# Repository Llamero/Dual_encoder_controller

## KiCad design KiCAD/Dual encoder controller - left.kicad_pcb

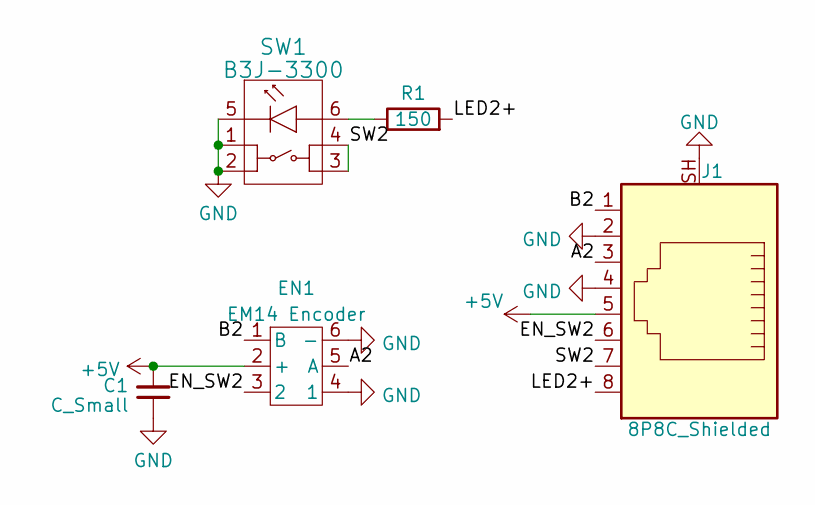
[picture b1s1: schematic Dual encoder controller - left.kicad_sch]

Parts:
C1: C_Small; C_Rect_L4.0mm_W2.5mm_P2.50mm; Part RCER71H105K2DBH03A
EN1: EM14 Encoder; EM14R0B-M25-L064S; Part EM14R0B-M25-L064S
J1: 8P8C_Shielded; ASSMANN_A-2004-2-4-LPS-N-R; Part A-2004-2-4-LPS-N-R
R1: 150; R_Axial_DIN0207_L6.3mm_D2.5mm_P7.62mm_Horizontal; Part LR1F150R
SW1: B3J-3300; Part B3J-3300

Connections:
+5V: C1.2, EN1.2 (+), J1.5
/A2: EN1.5 (A), J1.3
/B2: EN1.1 (B), J1.1
/EN_SW2: EN1.3 (2), J1.6
/LED2+: J1.8, R1.2
/SW2: J1.7, SW1.3, SW1.4
GND: C1.1, EN1.4 (1), EN1.6 (-), J1.2, J1.4, J1.SH, SW1.1, SW1.2, SW1.5
unnamed: R1.1, SW1.6

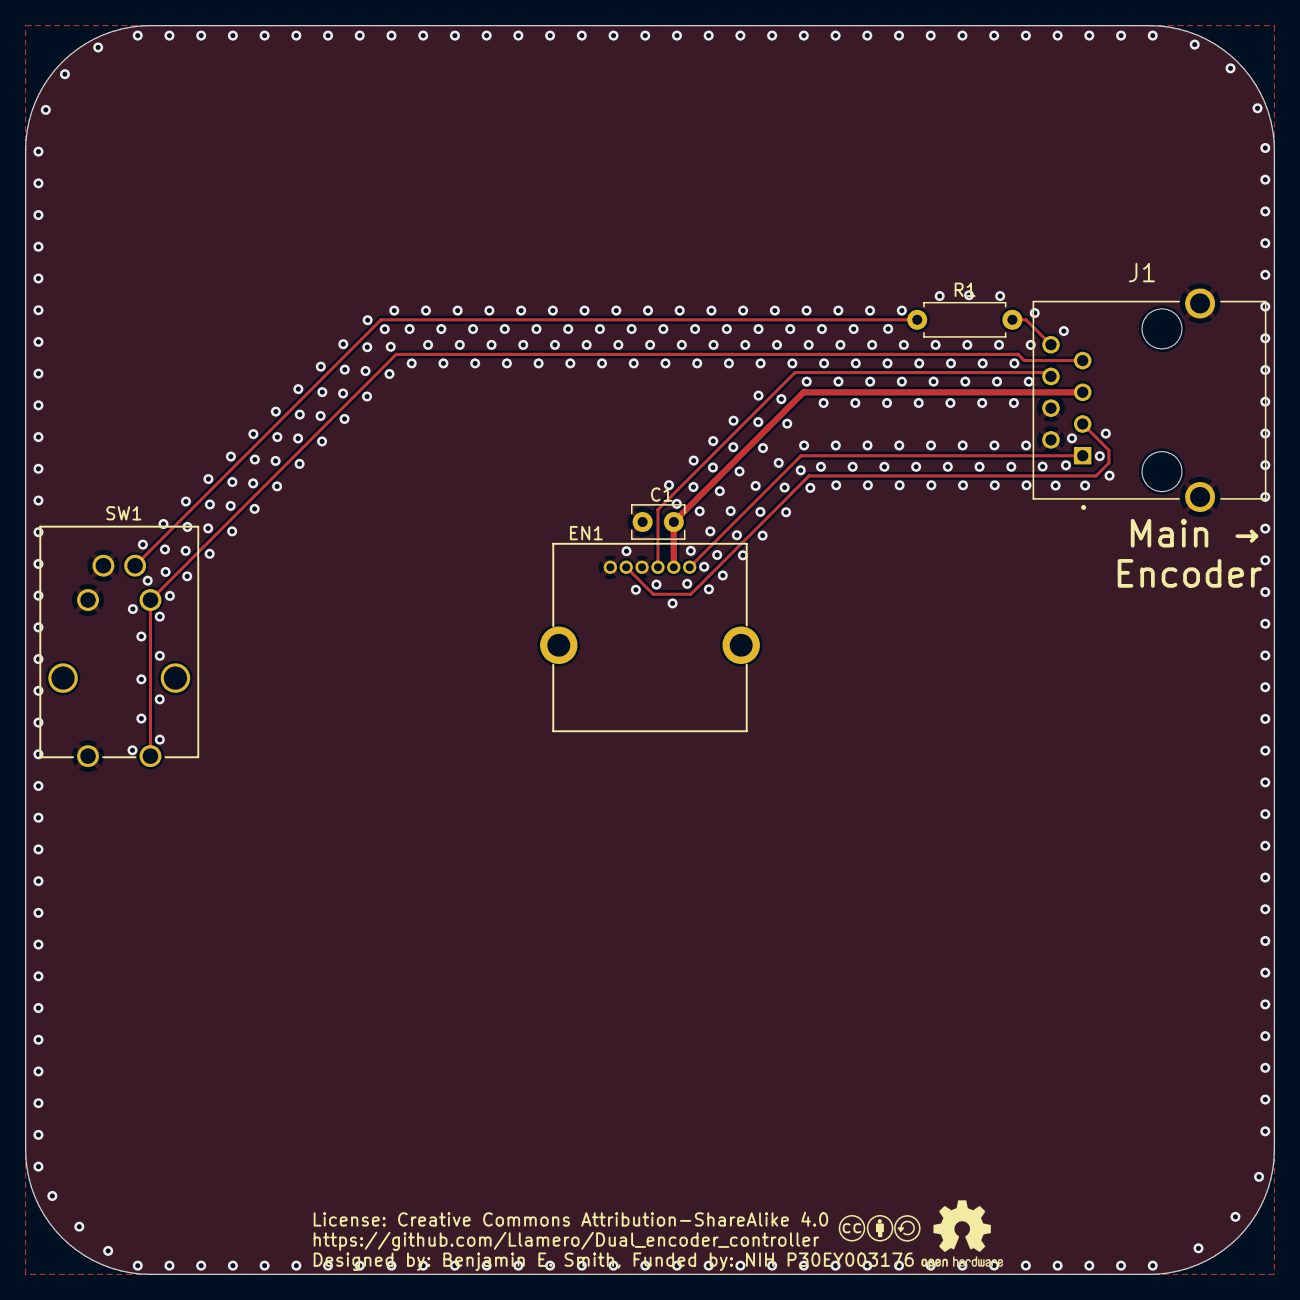
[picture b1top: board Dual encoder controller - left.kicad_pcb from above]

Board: 2 copper layers, 100.0 x 100.0 mm, 7 parts (0 on the bottom side), 8 nets.

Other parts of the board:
LOGO1: CC license; Creative_commons_license
LOGO3: OSHW Logo; OSHW-Logo2_7.3x6mm_SilkScreen

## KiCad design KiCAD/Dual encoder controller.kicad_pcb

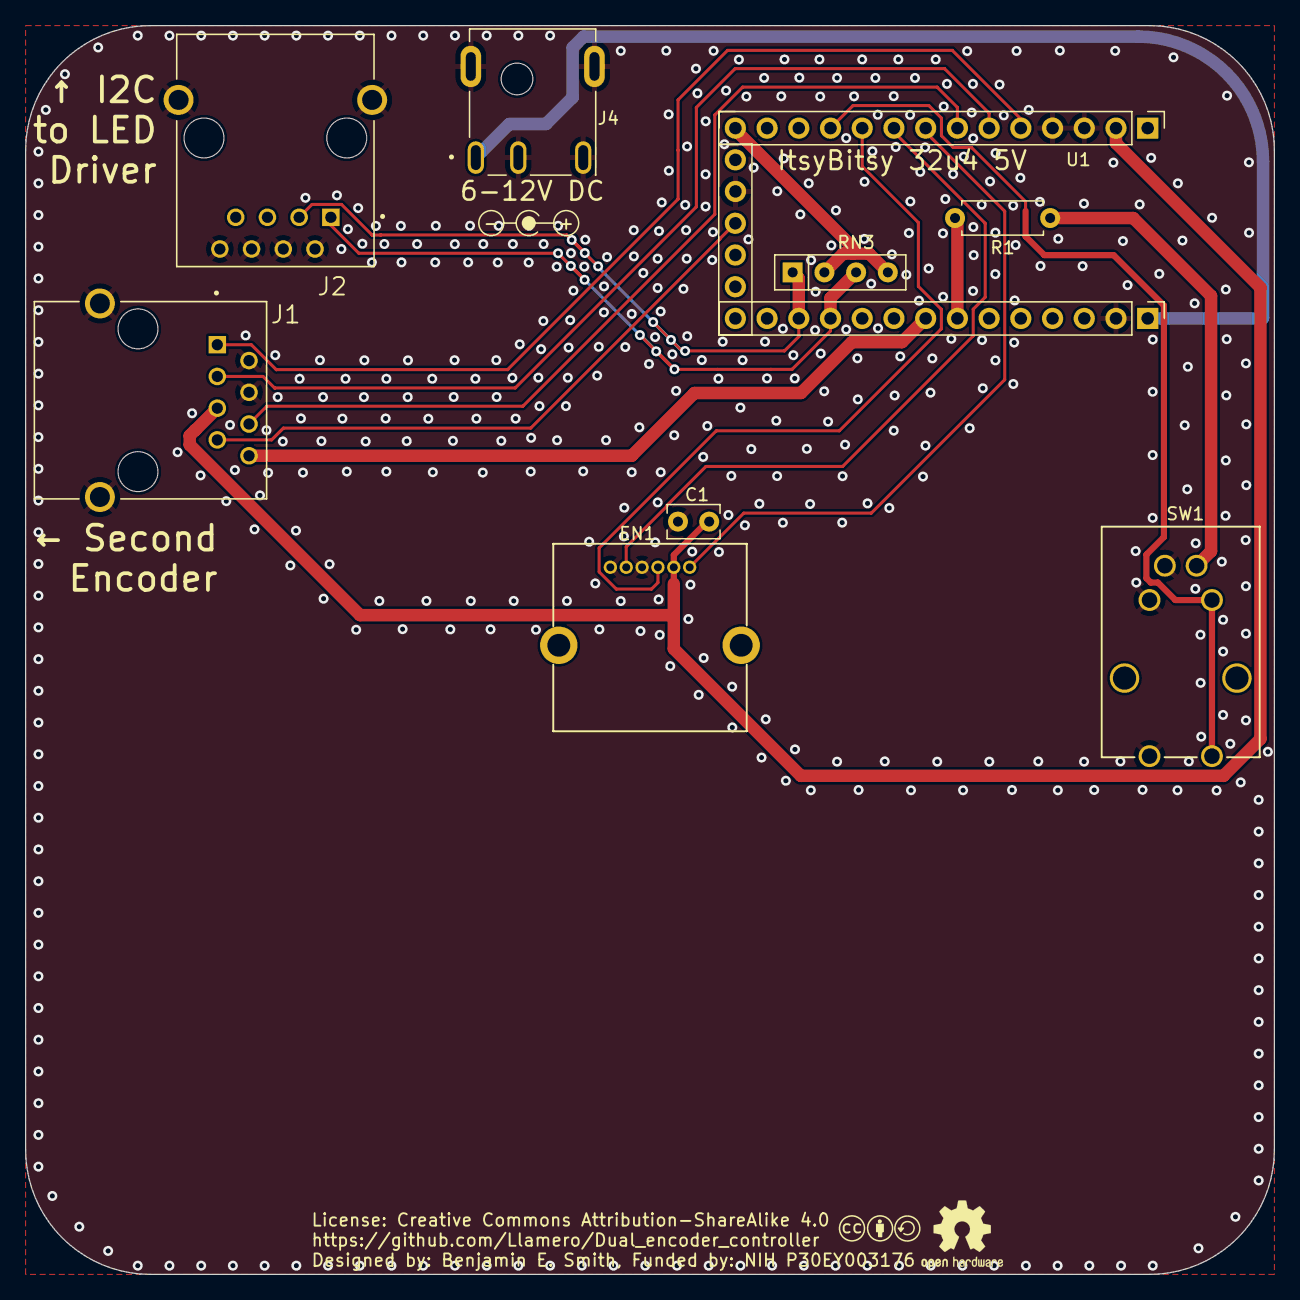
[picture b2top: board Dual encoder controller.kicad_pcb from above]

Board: 2 copper layers, 100.0 x 100.0 mm, 12 parts (0 on the bottom side), 17 nets.

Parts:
C1: C_Small; C_Rect_L4.0mm_W2.5mm_P2.50mm
EN1: EM14 Encoder; EM14R0B-M25-L064S
J1, J2: 8P8C_Shielded; ASSMANN_A-2004-2-4-LPS-N-R
J4: 2.5x5.5 Barrel Jack; TENSILITY_54-00128-DC Jack
LOGO1: CC license; Creative_commons_license
LOGO2: Jack Polarity; Polarity_Center_Positive
LOGO3: OSHW Logo; OSHW-Logo2_7.3x6mm_SilkScreen
R1: 150; R_Axial_DIN0207_L6.3mm_D2.5mm_P7.62mm_Horizontal
RN3: 470; R_Array_SIP4
SW1: B3J-3300
U1: Itsy_Bitsy_32u4; Itsy Bitsy 32u4

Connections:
+3.3V: RN3.2 (R1.2), RN3.4 (R2.2), U1.14 (3.3V)
+5V: C1.2, EN1.2 (+), J1.5, U1.2 (5V)
+9V: J4.1, U1.33 (VBat)
/A1: EN1.5 (A), U1.9 (22_A4)
/A2: J1.3, U1.6 (19_A1)
/B1: EN1.1 (B), U1.8 (21_A3)
/B2: J1.1, U1.5 (18_A0)
/EN_SW1: EN1.3 (2), U1.10 (23_A5)
/EN_SW2: J1.6, U1.7 (20_A2)
/LED1+: R1.2, U1.27 (~10_A10)
/LED2+: J1.8, U1.26 (~9_A9)
/SCL: J2.1, RN3.3 (R2.1), U1.23 (~3_SCL)
/SDA: J2.3, RN3.1 (R1.1), U1.22 (2_SDA)
/SW1: SW1.3, SW1.4, U1.11 (15_SCK)
/SW2: J1.7, U1.17 (8_A8)
GND: C1.1, EN1.4 (1), EN1.6 (-), J1.2, J1.4, J1.SH, J2.2, J2.4, J2.6, J2.8, J2.SH, J4.2, J4.3, J4.MP (MountPin), SW1.1, SW1.2, SW1.5, U1.3 (ARef), U1.4 (GND), U1.16 (Gnd), U1.32 (Gnd)
unnamed: R1.1, SW1.6

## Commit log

2024-08-20 Initial design upload
2024-08-20 Add encoder bypass and guard vias
2024-08-21 Finished working draft
2024-08-21 Both boards pass DRC
2024-08-23 Add gerber
2024-10-12 Working code implementation of encoders and buttons
2024-10-22 Add example send and receive I2C code
2025-04-05 Add draft of USB protocol
2025-04-08 GUI can find and connect to controller
    Had to use PySerial as an initial port opener, PyQt5 cannot rx unless another library opens the port first.
2025-04-08 Fixed issue with waitForBytesWritten() returning error 12
    https://forum.qt.io/topic/41833/solved-qserialport-waitforbyteswritten-returns-false
2025-04-08 update controller name works!
2025-04-09 Demo with working LEDs!
2025-04-10 Fully implemented status

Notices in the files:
KiCAD/Dual encoder controller - left.kicad_pcb:
License: Creative Commons Attribution-ShareAlike 4.0
